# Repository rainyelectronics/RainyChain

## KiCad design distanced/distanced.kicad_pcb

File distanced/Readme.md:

#V1.0 Notes
- Haven't been able to burn the boot loader this could either be because of the circuit design or the soldering process.
  - check ICSP circuit, uC reset switch, check for short circuits.
- Power stage working properly RAW->3.3V->2.8V
- Have not been able to test the distance sensor
-

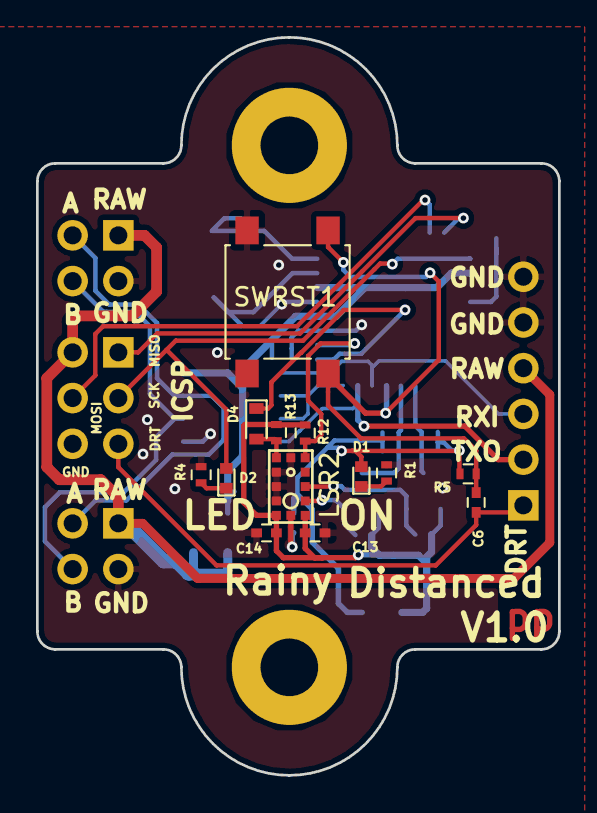
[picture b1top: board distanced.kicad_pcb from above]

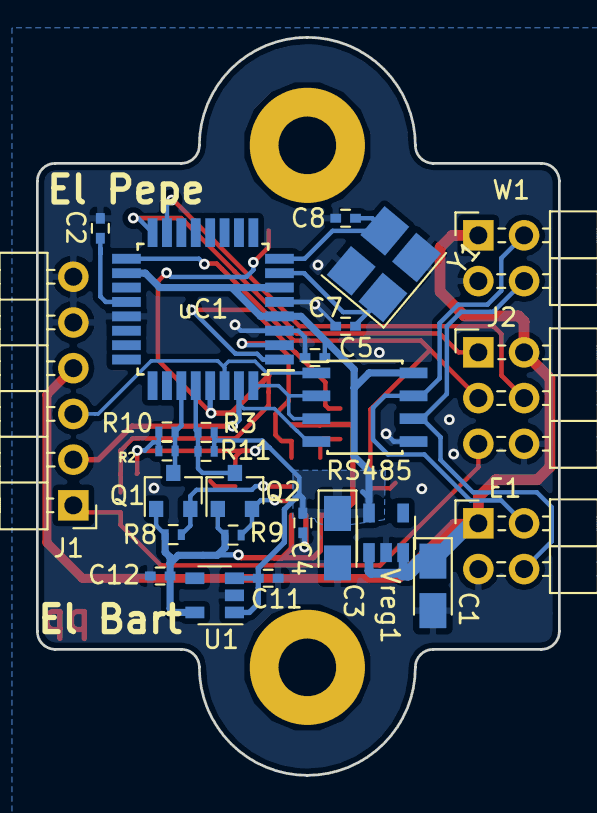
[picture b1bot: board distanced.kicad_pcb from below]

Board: 2 copper layers, 29.0 x 41.0 mm, 39 parts (26 on the bottom side), 26 nets.

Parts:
C1, C3: 10uF; CP_Tantalum_Case-A_EIA-3216-18_Reflow
C2, C4, C5, C6: 0.1uF; C_0402
C7, C8: 22nF; C_0402
C11, C12: 10uF; C_0402
C13: 100nF; C_0402
C14: 4.7uF; C_0402
D1: LED; LED_0402
D2: LED_GREEN; LED_0402
D4: D_Small; D_0603
E1: Econn; Pin_Header_Angled_2x02_Pitch2.54mm
J1: FTDI prog; Pin_Header_Angled_1x06_Pitch2.54mm
J2: ICSP; Pin_Header_Angled_2x03_Pitch2.54mm
LSR2: VL53L0X
Q1, Q2: BSS138; SOT-23
R1, R2, R3, R5, R8, R9, R10, R11, R12, R13: 10K; R_0402
R4: 330; R_0402
RS485: SP3485CN; SOIC-8_3.9x4.9mm_Pitch1.27mm
SWRST1: Reset; SW_SPST_B3S-1000
U1: MIC5205-2.8; SOT-23-5
Vreg1: MIC5205-3.3; SOT-23-5
W1: Wconn; Pin_Header_Angled_2x02_Pitch2.54mm
Y1: Crystal_GND24; Crystal_SMD_3225-4pin_3.2x2.5mm_HandSoldering
uC1: ATMEGA328P-AU; TQFP-32_7x7mm_Pitch0.8mm

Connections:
2.8_SCL: LSR2.10, Q2.2, R9.2
2.8_SDA: LSR2.9, Q1.2, R8.2
+2V8: C12.1, C13.1, C14.1, LSR2.1, LSR2.11, Q1.1, Q2.1, R8.1, R9.1, R12.1, R13.1, U1.5
+3V3: C3.1, C4.1, C5.1, C11.1, D1.2, R2.1, R3.1, R5.1, R10.1, R11.1, RS485.8, U1.1, U1.3, Vreg1.5, uC1.4, uC1.6, uC1.18
A: E1.4, RS485.6, W1.4
A4: Q1.3, R2.2, R10.2, uC1.27
A5: Q2.3, R3.2, R11.2, uC1.28
B: E1.2, RS485.7, W1.2
D2: RS485.2, RS485.3, uC1.32
D3: D4.1, uC1.1
D4: LSR2.7, R12.2, uC1.2
D11: J2.4, uC1.15
D12: J2.1, uC1.16
D13: D2.2, J2.3, uC1.17
DRT: C6.2, J1.1, J2.5
GNDREF: C1.2, C2.1, C3.2, C4.2, C5.2, C7.2, C8.2, C11.2, C12.2, C13.2, C14.2, E1.3, J1.5, J1.6, J2.6, LSR2.2, LSR2.3, LSR2.4, LSR2.6, LSR2.12, R1.2, R4.1, RS485.5, SWRST1.2, U1.2, Vreg1.2, W1.3, Y1.2, Y1.4, uC1.3, uC1.5, uC1.21
unnamed: C2.2, uC1.20
unnamed: C6.1, R5.2, SWRST1.1, uC1.29
unnamed: C7.1, Y1.1, uC1.7
unnamed: C8.1, Y1.3, uC1.8
unnamed: D1.1, R1.1
unnamed: D2.1, R4.2
unnamed: D4.2, LSR2.5, R13.2
RAW: C1.1, E1.1, J1.4, J2.2, Vreg1.1, Vreg1.3, W1.1
RXI: J1.3, RS485.1, uC1.30
TXO: J1.2, RS485.4, uC1.31

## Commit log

2018-11-18 The initial distance sensor files
2018-11-30 Added the folder with the ToF sensor symbol and footprint
2018-12-08 better schematic
2018-12-28 first routing done, ready for revision and being lectured
2018-12-28 modified reference text on the board
2018-12-28 minor changes
2019-02-15 Added the used component libraries to the project
2019-03-05 Updating the PCB to fit the requirements for PCBway
2019-03-06 Ready for production
    Modified silk screen to easy soldering and debugging
2019-03-06 Added the fabrication files
2019-03-23 added the BOM
2019-04-27 Added a readme for the distanced project
2019-05-01 Added PDF of the circuit for debugging
2019-05-01 Added pictures of the top and bottom
